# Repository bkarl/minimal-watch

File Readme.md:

# minimal-watch
This repo contains hardware and software for a minimalistic smartwatch. 

## Design goals

* step counter
* battery life of >= one year
* NFC data exchange
* powered by a coin cell
* fits a Casio F-91 W housing
* binary or hex time display using 12 bicolor LEDs
* brightness sensor to dim LEDs

## Issues in hw v0.0.1
* swapped SCL/SDA lines
* missing pull up on NFC interrupt line (BOOT0 does not have an internal pull up)
* wakeup sources (BMA400 or NFC) are not connected to WKUP pins so standby mode is not possible
* resistor for green LEDs is too large
* NFC antenna circuit is not working (coil had to be crafted by hand and glued to housing)

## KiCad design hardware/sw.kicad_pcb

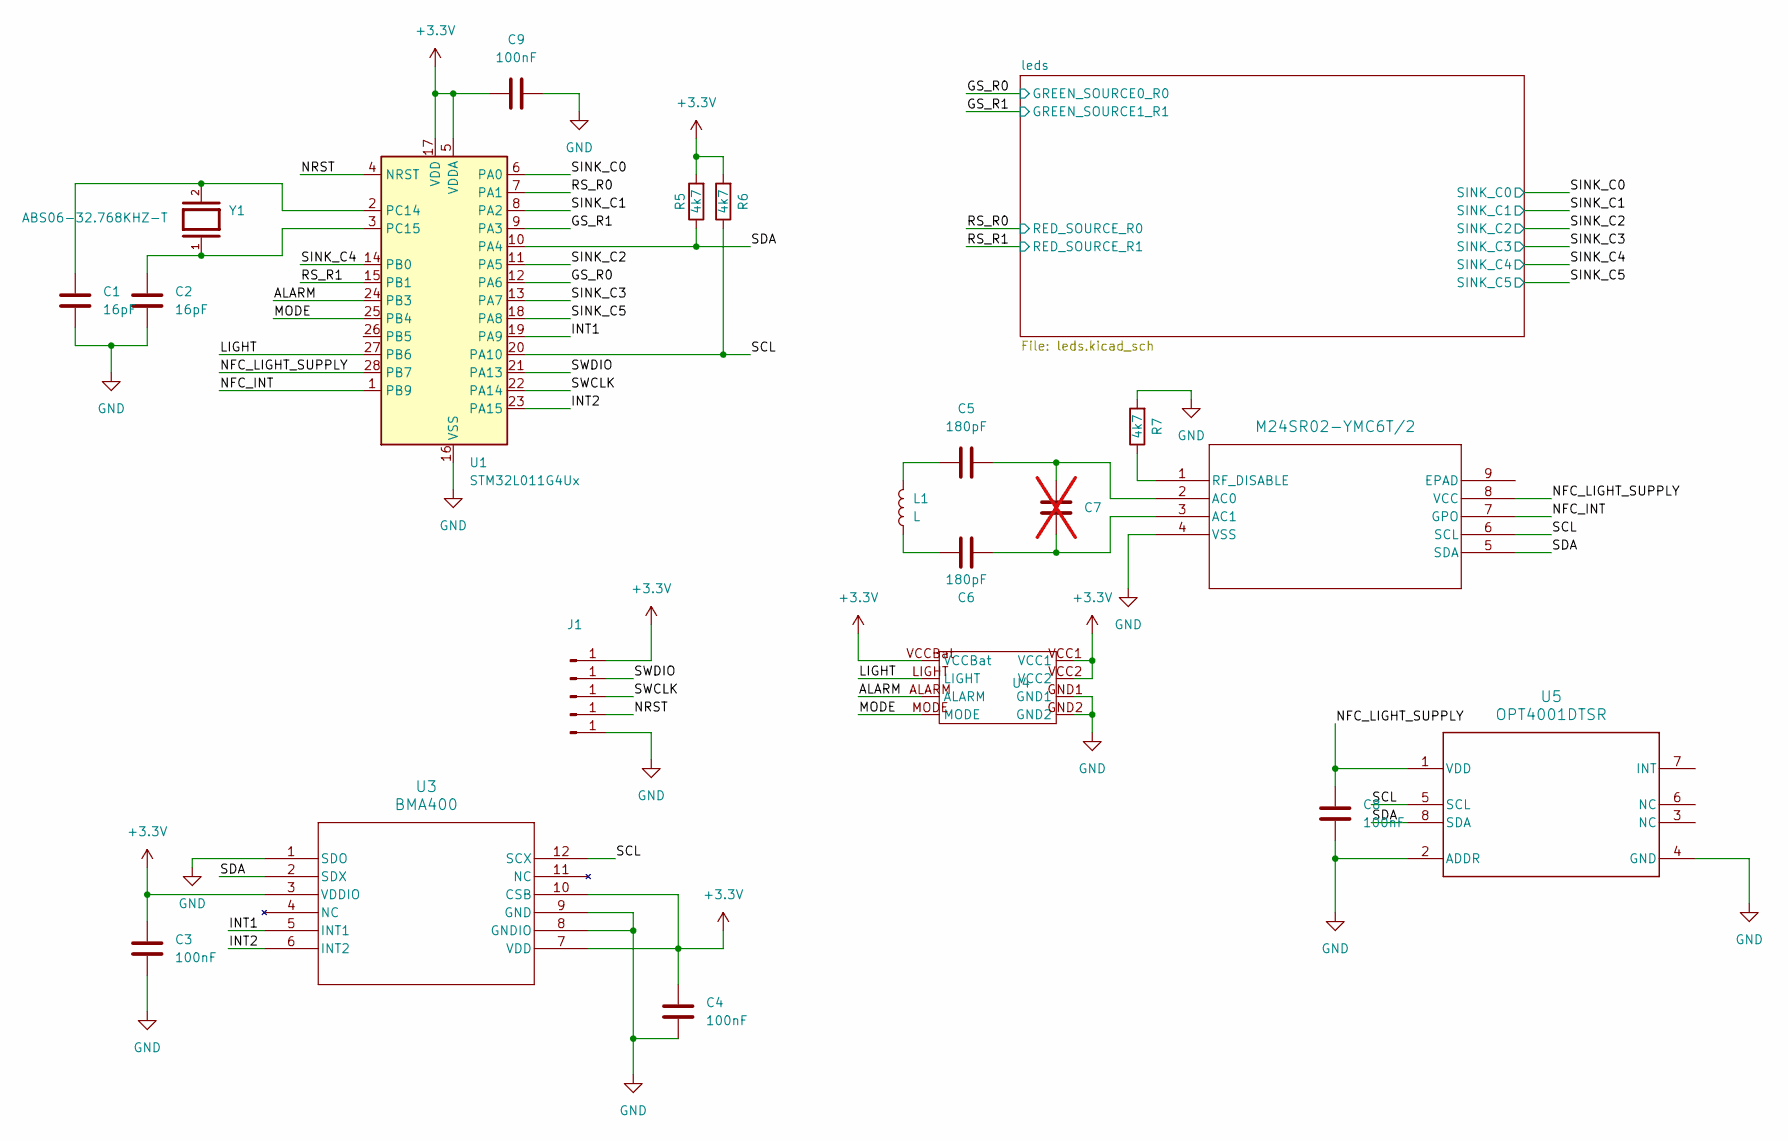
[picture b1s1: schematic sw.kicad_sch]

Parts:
C1, C2: 16pF; C_0402_1005Metric_Pad0.74x0.62mm_HandSolder
C3, C4, C8, C9: 100nF; C_0402_1005Metric_Pad0.74x0.62mm_HandSolder
C5, C6: 180pF; C_0402_1005Metric_Pad0.74x0.62mm_HandSolder
C7: C_0402_1005Metric_Pad0.74x0.62mm_HandSolder; not fitted
J1, J2, J3, J4, J5: Conn_01x01_Pin; SolderWirePad_1x01_SMD_1x2mm
L1: L; AANI-CH-0029
R5, R6, R7: 4k7; R_0402_1005Metric
U1: STM32L011G4Ux; QFN-28_4x4mm_P0.5mm
U2: M24SR02-YMC6T/2; UFDFPN8_M24SR02_STM
U3: BMA400; QFN_BMA400_BOS
U4: CASIO-F91W-OUTLINE-USB
U5: OPT4001DTSR; DTS0008A-MFG
Y1: ABS06-32.768KHZ-T; XTAL_ABS06-32.768KHZ-T; PARTREV 4/25/2022

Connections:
+3.3V: C3.1, C4.1, C9.1, J1.1, R5.2, R6.2, U1.5 (VDDA), U1.17 (VDD), U3.3 (VDDIO), U3.7 (VDD), U3.10 (CSB), U4.VCC1, U4.VCC2, U4.VCCBat
/ALARM: U1.24 (PB3), U4.ALARM
/GS_R0: U1.12 (PA6); also elsewhere on the board
/GS_R1: U1.9 (PA3); also elsewhere on the board
/INT1: U1.19 (PA9), U3.5 (INT1)
/INT2: U1.23 (PA15), U3.6 (INT2)
/LIGHT: U1.27 (PB6), U4.LIGHT
/MODE: U1.25 (PB4), U4.MODE
/NFC_INT: U1.1 (PB9), U2.7 (GPO)
/NFC_LIGHT_SUPPLY: C8.1, U1.28 (PB7), U2.8 (VCC), U5.1 (VDD)
/NRST: J4.1, U1.4 (NRST)
/RS_R0: U1.7 (PA1); also elsewhere on the board
/RS_R1: U1.15 (PB1); also elsewhere on the board
/SCL: R6.1, U1.20 (PA10), U2.6 (SCL), U3.12 (SCX), U5.5 (SCL)
/SDA: R5.1, U1.10 (PA4), U2.5 (SDA), U3.2 (SDX), U5.8 (SDA)
/SINK_C0: U1.6 (PA0); also elsewhere on the board
/SINK_C1: U1.8 (PA2); also elsewhere on the board
/SINK_C2: U1.11 (PA5); also elsewhere on the board
/SINK_C3: U1.13 (PA7); also elsewhere on the board
/SINK_C4: U1.14 (PB0); also elsewhere on the board
/SINK_C5: U1.18 (PA8); also elsewhere on the board
/SWCLK: J3.1, U1.22 (PA14)
/SWDIO: J2.1, U1.21 (PA13)
GND: C1.1, C2.2, C3.2, C4.2, C8.2, C9.2, J5.1, R7.2, U1.16 (VSS), U2.4 (VSS), U3.1 (SDO), U3.8 (GNDIO), U3.9 (GND), U4.GND1, U4.GND2, U5.2 (ADDR), U5.4 (GND)
unnamed: C5.1, L1.2
unnamed: C6.1, L1.1
unnamed: C1.2, U1.2 (PC14), Y1.2
unnamed: C2.1, U1.3 (PC15), Y1.1
unnamed: C5.2, C7.2, U2.2 (AC0)
unnamed: C6.2, C7.1, U2.3 (AC1)
unnamed: R7.1, U2.1 (RF_DISABLE)

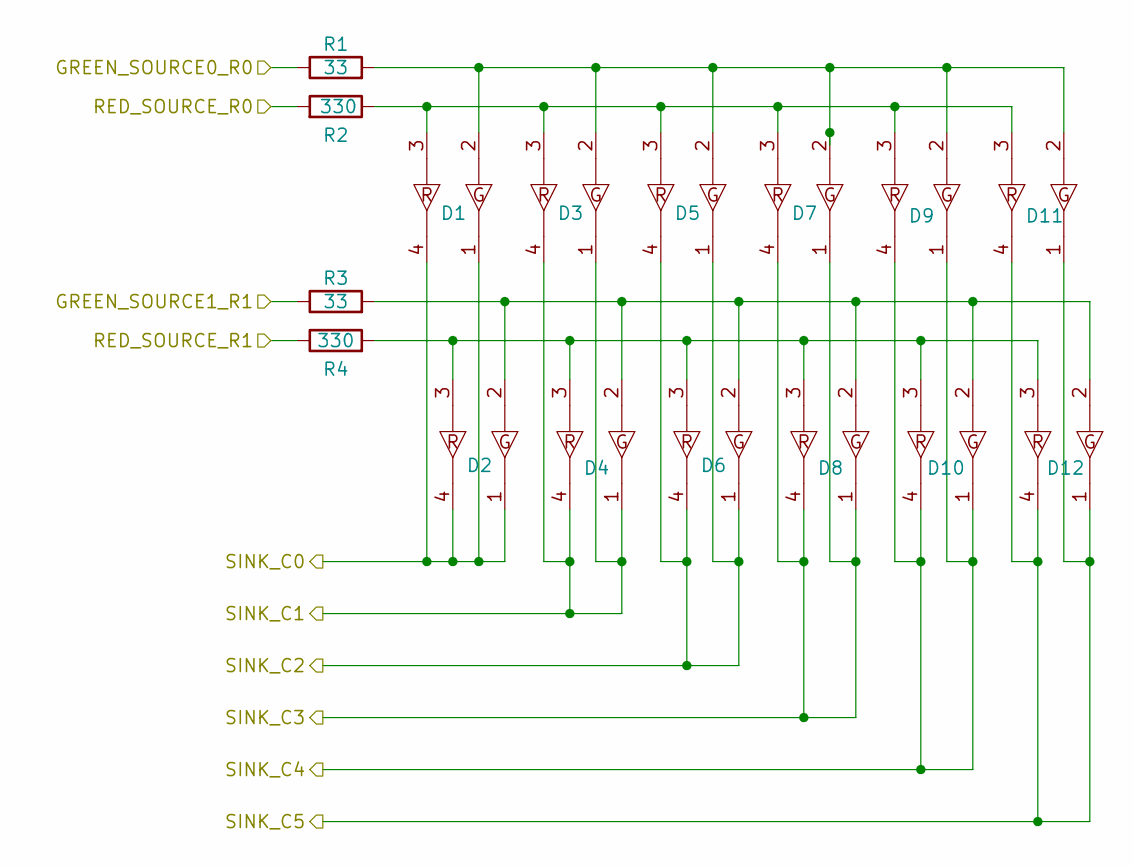
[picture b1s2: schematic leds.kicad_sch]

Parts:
D1, D2, D3, D4, D5, D6, D7, D8, D9, D10, D11, D12: WL-SBCD_150066RG54050
R1, R3: 33; R_0402_1005Metric
R2, R4: 330; R_0402_1005Metric

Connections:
/GS_R0: R1.1; also elsewhere on the board
/GS_R1: R3.1; also elsewhere on the board
/RS_R0: R2.2; also elsewhere on the board
/RS_R1: R4.1; also elsewhere on the board
/SINK_C0: D1.1, D1.4, D2.1, D2.4; also elsewhere on the board
/SINK_C1: D3.1, D3.4, D4.1, D4.4; also elsewhere on the board
/SINK_C2: D5.1, D5.4, D6.1, D6.4; also elsewhere on the board
/SINK_C3: D7.1, D7.4, D8.1, D8.4; also elsewhere on the board
/SINK_C4: D9.1, D9.4, D10.1, D10.4; also elsewhere on the board
/SINK_C5: D11.1, D11.4, D12.1, D12.4; also elsewhere on the board
unnamed: D1.2, D3.2, D5.2, D7.2, D9.2, D11.2, R1.2
unnamed: D1.3, D3.3, D5.3, D7.3, D9.3, D11.3, R2.1
unnamed: D2.2, D4.2, D6.2, D8.2, D10.2, D12.2, R3.2
unnamed: D2.3, D4.3, D6.3, D8.3, D10.3, D12.3, R4.2

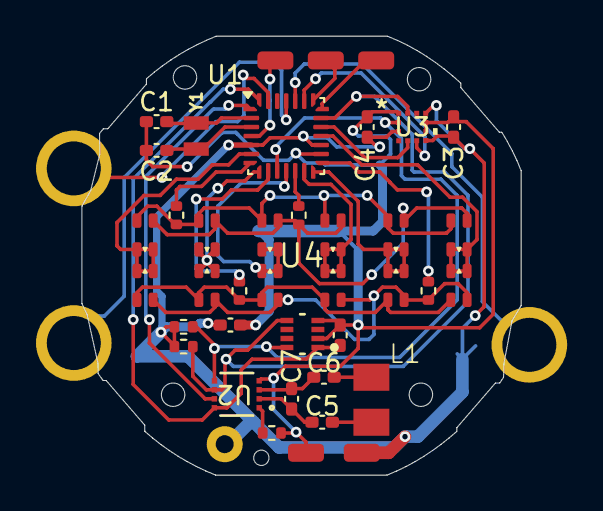
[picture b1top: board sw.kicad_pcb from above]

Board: 2 copper layers, 24.4 x 24.4 mm, 40 parts (0 on the bottom side), 35 nets.

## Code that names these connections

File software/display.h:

#pragma once

#include "stm32l0xx_hal.h"

#define N_ROWS 2
#define N_COLUMNS 6
#define N_COLORS 2

typedef enum {
    DISPLAY_MODE_TIME,
    DISPLAY_MODE_STEPS,
    DISPLAY_MODE_SECONDS
} display_mode_t;

typedef struct {
    unsigned current_column;
    uint8_t red_vals[N_ROWS];
    uint8_t green_vals[N_ROWS];
} display_state_t;

typedef struct {
    unsigned pin_idx;
    GPIO_TypeDef* gpio;
} pin_mapping_t;

/*
Display has the following structure:
Row 0: LED 5 .... LED 0
Row 1: LED 5 .... LED 0
Each LED has two colors. The LSB is on the right side.
*/

#define SINK_C0_PIN GPIO_PIN_0

#define SINK_C1_PIN GPIO_PIN_2

#define SINK_C2_PIN GPIO_PIN_5

#define SINK_C3_PIN GPIO_PIN_7

#define SINK_C4_PIN GPIO_PIN_0
#define SINK_C5_PIN GPIO_PIN_8

#define RED_SOURCE_ROW_0    GPIO_PIN_1
#define RED_SOURCE_ROW_1    GPIO_PIN_1

#define GREEN_SOURCE_ROW_0    GPIO_PIN_6
#define GREEN_SOURCE_ROW_1    GPIO_PIN_3

#define STEP_PER_DAY_TARGET 10000
#define STEPS_PER_TICK STEP_PER_DAY_TARGET/N_COLUMNS

void display_init();
void display_init_gpio();
void display_switch_all_off();
void display_iterate_column();
void switch_row_color_if_enabled(pin_mapping_t *row_pin_mapping, uint8_t row_val, unsigned row_idx);
void display_set_step_ctr(uint8_t *pixel_reg);
void display_init_timer();
void display_set_time();
void display_shutdown();
void display_update();

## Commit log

2024-12-01 initial
2024-12-01 corrected title
2024-12-01 more infos
2024-12-04 added sw
2024-12-18 sketches
2024-12-18 sketching
2024-12-18 cleanup
2024-12-21 added i2c bitbanging code
2024-12-21 added initial bma400 code for testing
2024-12-23 display sim
2024-12-24 added quartet mode
2024-12-24 add some space
2024-12-25 added interrupt code
2024-12-31 correct pins
2025-01-03 fix i2c
2025-01-04 init code
2025-01-05 fixed bma400 initialisation
2025-01-05 added timer to enter stop mode
2025-01-07 enter sleep mode the right way
2025-01-11 added nfc code
2025-01-22 dont use hal for lptim
2025-01-26 removed hal timer code
2025-02-05 interaction with app
2025-02-05 wip state handling, enable i2c internal pull ups
2025-02-06 more state handling
2025-02-08 nfc memory access
2025-02-12 step counter stuff
2025-02-13 nfc tests
2025-02-15 added sceond alarm, stage handling
2025-03-03 enable wip interrupt
2025-03-04 check if nfc is ready
2025-03-16 added more display modes
2025-03-16 enable step counter
2025-03-22 added kicad data
2025-03-22 keep track of issues
